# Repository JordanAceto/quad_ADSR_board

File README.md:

# Quad digital ADSR module

# *** Work in progress ***

## ADSRs are generated by an STM32 microcontroller and controlled by four encoders. A seven-segment display shows the most recently modified parameter.

One ADSR at a time is set as the "active" ADSR, which will be controlled by the encoders.

To select an ADSR as "active", the encoder push-button above a given ADSR is pressed.

The four-digit seven-segment display shows the parameter of the encoder that was most recently turned. For instance, if you just turned the decay time to 500 milliseconds, the display will show `0.500`. If you then adjust the sustain level to 68%, the display will now show `  68`. Time based parameters are shown in units of seconds, and sustain parameters are shown as 0% to 100%.

Additionally, the ADSRs can all be forced to lock to a "master" ADSR, so that that their attack, decay, sustain, and release parameters are all set the same. The four ADSRs can still be triggered independently in this mode, which makes this useful for polyphonic patches. This saves you from manually setting identical paramters four times. Lock-to-master mode is selected by performing a long push-switch press of the encoder above the desired ADSR. For instance, to force all the ADSRs to lock to the ADSR 3 settings, depress and hold the sustain encoder push-button for a few seconds. To leave lock-to-master mode, do a short click of any of the encoder push-buttons to select a new active ADSR.

A bank of four bi-color LEDs shows the active ADSR, and whether it is in independent, or lock-to-master mode.

# First rev build evaluation:
- Most of the systems work.
- __Done__ (but there is an I2C bug lurking, see the issues)~~The EEPROM has not been physically installed and EEPROM code has not been written yet.~~
- __DONE__ ~~In the code, when switching from lock-to-master mode back to independent mode: the ADSRs should go back to the settings they held before entering lock-to-master mode. Write a function called `release_ADSRs_from_master_mode` or something that accomplishes this, and call that function when leaving lock-to-master mode~~.
- __Done__ ~~The encoders should be no-detent types. I used encoders with detents and I don't like it.~~
- I tried and failed to setup encoder trigger filtering, please investigate using the timer register filters when the timers are in encoder mode. I'd like to be able to apply filtering to the encoders. They work fine and don't misfire now, but it would be nice to easily tailor how "fast" they update by addign in some filtering.
- __This really isn't that bad__ ~~The heights of the panel mount components is an issue: the 3.5mm jacks are taller than the encoders and the seven-segment display. I got everything to work by lifting the encoders and 7-seg up off the pcb before soldering, but this is lame. I think the solution is split the pcb into a main pcb and a jack pcb, and connect the two pcbs with wires. Another solution could be to create a "lifter" pcb that acts as a spacer between the main pcb and the encoders/7-seg, but this seems kind of yucky too. Think about this for a while before doing a new pcb rev.~~
- I'm having issues with getting the PLL to work for arbitrary frequencies: with some settings of M, N, and P the output frequency is not as expected. Please investigate this and figure out what I'm doing wrong.
- I used two MCP4822 DACs, but I probably could have used the 2 internal DAC channels for 2 of the ADSRs and only installed one MCP4822. Investigate if using the internal DAC for 2 channels creates any pinout conflicts, or any other kind of conflicts, for the next board revision, to try and save a DAC.
- The ADSR outputs are low: I want 10v peak ADSRs and I calculated the opamp gain resistors assuming the DACs output 3.3v peaks, but they don't. Please recalculate the gain resistors for the actual MCP4822 output with a gain of 1x. Take into account the internal DACs if you apply the suggestion above.
- __DONE__ (enabled FPU and changed signals to floats) ~~Many parts of the codebase could be optimized and improved. In particular, the ADSR code does some costly 64-bit divisions in a couple of spots. See if you can't improve this. View the `main.list` output file occasionally~~.
- __DONE__ (works ok but be on the lookout) ~~Compiler optimization is turned off right now. Turn this up to `-Os` or `-O2` and make sure that nothing breaks. There might be some volatile issues, or necessary code that gets optimized away, be careful and thorough!~~
- Otherwise the project is in pretty good shape! The prototype I built could definitely go in a rack and work with other modules.

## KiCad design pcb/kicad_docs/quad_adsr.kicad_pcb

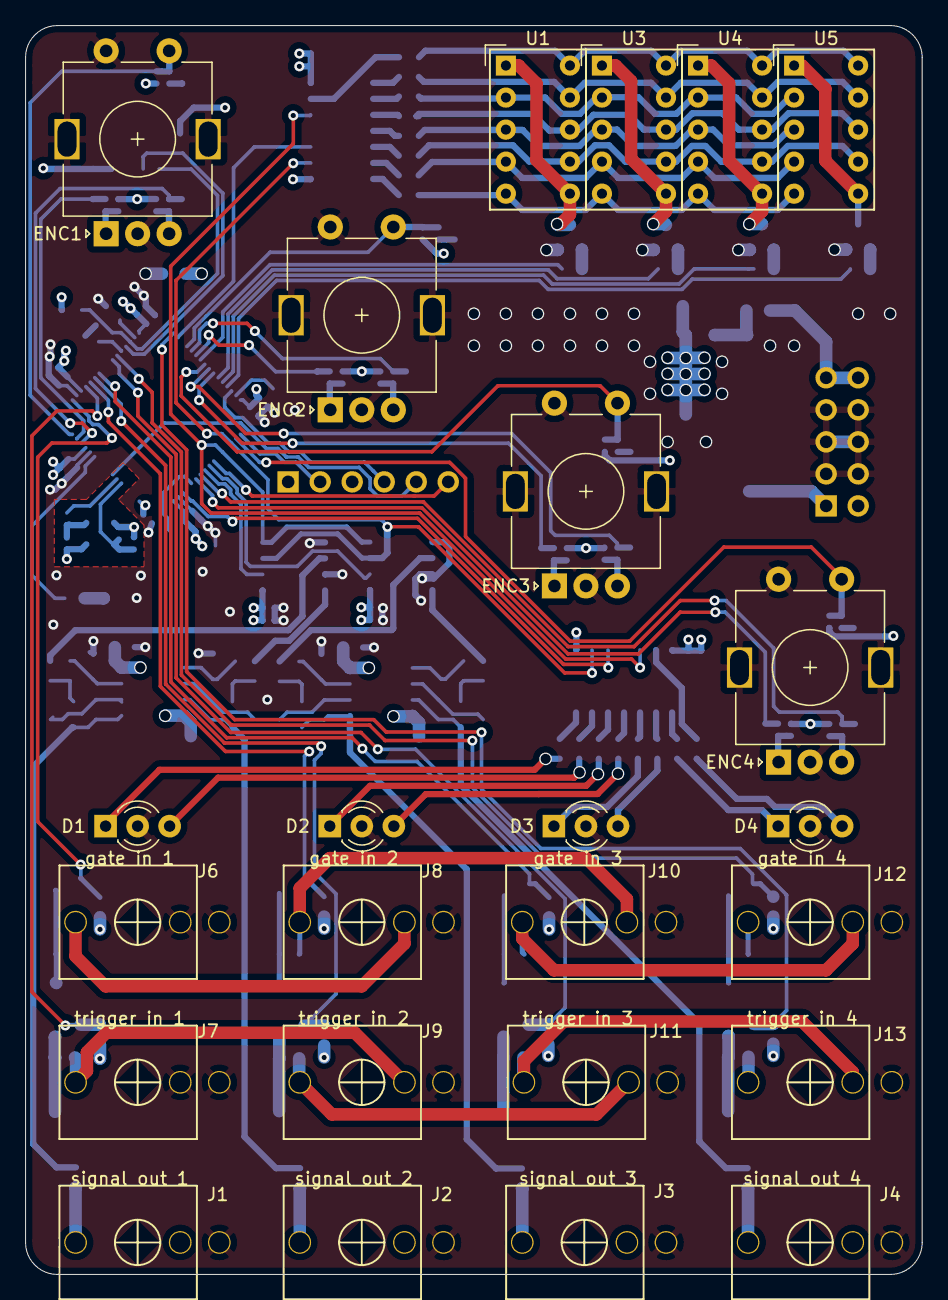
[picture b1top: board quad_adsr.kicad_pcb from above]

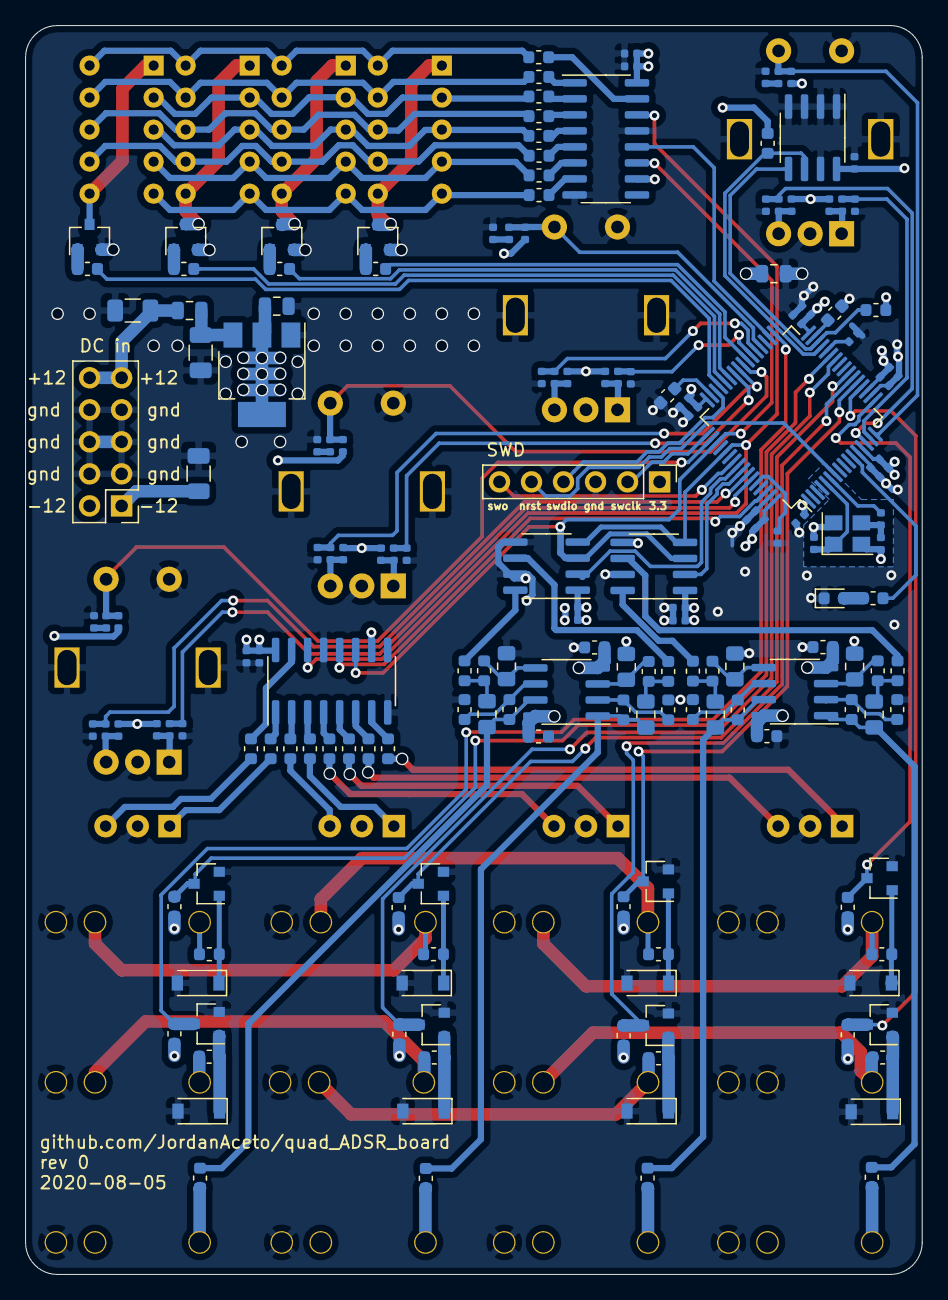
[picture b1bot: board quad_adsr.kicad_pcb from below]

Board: 4 copper layers, 71.1 x 99.1 mm, 197 parts (173 on the bottom side), 142 nets.

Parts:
C1, C2, C4, C5, C7, C8, C10, C11: 10nF; C_0402_1005Metric
C3, C6, C9, C12, C16, C17, C18, C19, C20, C21, C22, C23, C24, C25, C26, C27, C28, C29, C30, C31, C32, C49, C50, C53: 100nF; C_0402_1005Metric
C13, C51, C52: 10uF; C_1206_3216Metric
C14, C15: 10uF; C_0805_2012Metric
C33, C34, C35, C36: 100nF; C_0603_1608Metric
C37, C38, C39, C40, C41, C42, C43, C44: 2n2; C_0805_2012Metric_Pad1.15x1.40mm_HandSolder
C45, C46: 2.2uF; C_0603_1608Metric
C47, C48: 12pF; C_0402_1005Metric
D1, D2, D3, D4: LED_Dual_ACA; LED_D3.0mm-3
D5: LED; LED_0603_1608Metric
D6, D7, D8, D9, D10, D11, D12, D13: 1N4148W; D_SOD-123
ENC1, ENC2, ENC3, ENC4: Rotary_Encoder_Switch; RotaryEncoder_Alps_EC11E-Switch_Vertical_H20mm
FB1: Ferrite_Bead_Small; L_0805_2012Metric
HSE1: 16MHz; Crystal_SMD_3225-4Pin_3.2x2.5mm
J1, J2, J3, J4: PJ301M-12
J5: power_in; PinHeader_2x05_P2.54mm_Vertical
J6: gate_1_i n; PJ301M-12
J7: trigger_1_in; PJ301M-12
J8: gate_2_in; PJ301M-12
J9: trigger_2_in; PJ301M-12
J10: gate_3_in; PJ301M-12
J11: trigger_3_in; PJ301M-12
J12: gate_4_in; PJ301M-12
J13: trigger_4_in; PJ301M-12
J14: SWD_header; PinHeader_1x06_P2.54mm_Vertical
Q1, Q2, Q3, Q4, Q5, Q6, Q7, Q8, Q9, Q10, Q11, Q12: MMBT3904; SOT-23
R1, R2, R3, R4, R7, R8, R9, R10, R13, R14, R15, R16, R19, R20, R21, R22, R82, R83: 10k; R_0402_1005Metric
R5, R11, R17, R23: 4k7; R_0402_1005Metric
R6, R12, R18, R24, R84: 100; R_0402_1005Metric
R25, R34, R35, R36, R50, R52, R54, R56, R58, R60, R62, R64: 10k; R_0603_1608Metric
R26, R27, R28, R29, R30, R31, R32, R33, R37, R38, R39, R40, R41, R42, R43, R44: 390; R_0603_1608Metric
R45, R46, R47, R48: 1k; R_0603_1608Metric
R49, R51, R53, R55, R57, R59, R61, R63: 100k; R_0603_1608Metric
R65, R66, R73, R74: 50k; R_0603_1608Metric
R67, R68, R75, R76: 200k; R_0603_1608Metric
R69, R70, R77, R78: 33k; R_0603_1608Metric
R71, R72, R79, R80: 68k; R_0603_1608Metric
R81: 2k2; R_0603_1608Metric
R85, R86: 4k7; R_0603_1608Metric
U1, U3, U4, U5: HDSP-7503; HDSP-A151
U2, U6: 74HC595; SOIC-16_3.9x9.9mm_P1.27mm
U7: AMS1117-3.3; SOT-223-3_TabPin2
U8, U11: TL072; SOIC-8_3.9x4.9mm_P1.27mm
U9, U10: MCP4822; SOIC-8_3.9x4.9mm_P1.27mm
U12: STM32F405RGTx; LQFP-64_10x10mm_P0.5mm
U13: 24LC32; SOIC-8_3.9x4.9mm_P1.27mm

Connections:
+3V3: C14.1, C15.1, C16.1, C17.1, C18.1, C19.1, C20.1, C21.1, C22.1, C23.1, C24.1, C25.1, C26.1, C27.1, C28.1, C29.1, C30.1, C31.1, C32.1, C49.1, C50.1, C53.1, J14.1, R2.1, R3.1, R5.2, R8.1, R9.1, R11.1, R14.1, R15.1, R17.2, R20.1, R21.1, R23.1, R50.1, R52.1, R54.1, R56.1, R58.1, R60.1, R62.1, R64.1, R85.1, R86.1, U2.10, U2.16, U6.10, U6.16, U7.2, U9.1, U10.1, U12.1, U12.13, U12.19, U12.32, U12.48, U12.64, U13.8
+12V: C33.1, C35.1, C51.1, FB1.2, J5.9, J5.10, U8.8, U11.8
-12V: C34.2, C36.2, C52.2, J5.1, J5.2, U8.4, U11.4
/EEPROM/I2C2_SCL: R86.2, U12.29, U13.6
/EEPROM/I2C2_SDA: R85.2, U12.30, U13.5
/encoders/enc_1_a_out: C1.1, R1.2, U12.14
/encoders/enc_1_b_out: C2.1, R4.2, U12.15
/encoders/enc_1_sw_out: ENC1.S1, R5.1, R6.1, U12.16
/encoders/enc_2_a_out: C4.1, R7.2, U12.37
/encoders/enc_2_b_out: C5.1, R10.2, U12.38
/encoders/enc_2_sw_out: ENC2.S1, R11.2, R12.1, U12.36
/encoders/enc_3_a_out: C7.1, R13.2, U12.41
/encoders/enc_3_b_out: C8.1, R16.2, U12.42
/encoders/enc_3_sw_out: ENC3.S1, R17.1, R18.1, U12.40
/encoders/enc_4_a_out: C10.1, R19.2, U12.58
/encoders/enc_4_b_out: C11.1, R22.2, U12.59
/encoders/enc_4_sw_out: ENC4.S1, R23.2, R24.1, U12.50
/input_jacks/g_2_normalization: J8.3, J10.2, R53.2
/input_jacks/t_2_normalization: J9.3, J11.2, R55.2
/leds/QA: R37.2, U6.15
/leds/QB: R38.2, U6.1
/leds/QC: R39.2, U6.2
/leds/QD: R40.2, U6.3
/leds/QE: R41.2, U6.4
/leds/QF: R42.2, U6.5
/leds/QG: R43.2, U6.6
/leds/QH: R44.2, U6.7
/leds/spi_clk_in: U2.11, U6.11, U9.3, U10.3, U12.51
/leds/spi_data_in: U2.14, U6.14, U9.4, U10.4, U12.53
/leds/spi_rg_leds_cs: U6.12, U12.62
/seven_segment_display/digit_1_in: R25.2, U12.39
/seven_segment_display/digit_2_in: R34.2, U12.43
/seven_segment_display/digit_3_in: R35.2, U12.44
/seven_segment_display/digit_4_in: R36.2, U12.45
/seven_segment_display/segment_A: R26.1, U1.10, U3.10, U4.10, U5.10
/seven_segment_display/segment_B: R27.1, U1.9, U3.9, U4.9, U5.9
/seven_segment_display/segment_C: R29.1, U1.8, U3.8, U4.8, U5.8
/seven_segment_display/segment_D: R33.1, U1.5, U3.5, U4.5, U5.5
/seven_segment_display/segment_DP: R31.1, U1.7, U3.7, U4.7, U5.7
/seven_segment_display/segment_E: R32.1, U1.4, U3.4, U4.4, U5.4
/seven_segment_display/segment_F: R28.1, U1.2, U3.2, U4.2, U5.2
/seven_segment_display/segment_G: R30.1, U1.3, U3.3, U4.3, U5.3
/seven_segment_display/spi_seven_segment_cs: U2.12, U12.34
/spi_dacs_and_level_shifters/10vp_adsr_1_out: C39.1, R45.2, R71.1, U8.1
/spi_dacs_and_level_shifters/10vp_adsr_2_out: C43.1, R46.2, R79.1, U8.7
/spi_dacs_and_level_shifters/10vp_adsr_3_out: C40.1, R47.2, R72.1, U11.1
/spi_dacs_and_level_shifters/10vp_adsr_4_out: C44.1, R48.2, R80.1, U11.7
/spi_dacs_and_level_shifters/adsr_1_3.3v: R66.2, U9.6
/spi_dacs_and_level_shifters/adsr_2_3.3v: R74.2, U9.8
/spi_dacs_and_level_shifters/adsr_3_3.3v: R65.2, U10.6
/spi_dacs_and_level_shifters/adsr_4_3.3v: R73.2, U10.8
/spi_dacs_and_level_shifters/spi_dac1_cs: U9.2, U12.57
/spi_dacs_and_level_shifters/spi_dac2_cs: U10.2, U12.56
/stmf32/NRST: J14.5, U12.7
/stmf32/PH1: R84.1, U12.6
/stmf32/PHO: C47.1, HSE1.1, U12.5
/stmf32/SWCLK: J14.2, U12.49
/stmf32/SWDIO: J14.4, U12.46
/stmf32/SWO: J14.6, U12.55
/stmf32/gate_1_in: Q5.3, R50.2, U12.17
/stmf32/gate_2_in: Q7.3, R54.2, U12.21
/stmf32/gate_3_in: Q9.3, R58.2, U12.23
/stmf32/gate_4_in: Q11.3, R62.2, U12.27
/stmf32/status_led: R81.1, U12.11
/stmf32/trigger_1_in: Q6.3, R52.2, U12.20
/stmf32/trigger_2_in: Q8.3, R56.2, U12.22
/stmf32/trigger_3_in: Q10.3, R60.2, U12.26
/stmf32/trigger_4_in: Q12.3, R64.2, U12.33
GND: C1.2, C2.2, C3.2, C4.2, C5.2, C6.2, C7.2, C8.2, C9.2, C10.2, C11.2, C12.2, C13.2, C14.2, C15.2, C16.2, C17.2, C18.2, C19.2, C20.2, C21.2, C22.2, C23.2, C24.2, C25.2, C26.2, C27.2, C28.2, C29.2, C30.2, C31.2, C32.2, C33.2, C34.1, C35.2, C36.1, C37.2, C38.2, C41.2, C42.2, C45.2, C46.2, C47.2, C48.2, C49.2, C50.2, C51.2, C52.1, C53.2, D1.2, D2.2, D3.2, D4.2, D5.1, D6.2, D7.2, D8.2, D9.2, D10.2, D11.2, D12.2, D13.2, ENC1.C, ENC1.MP, ENC1.S2, ENC2.C, ENC2.MP, ENC2.S2, ENC3.C, ENC3.MP, ENC3.S2, ENC4.C, ENC4.MP, ENC4.S2, HSE1.2, HSE1.4, J1.1, J2.1, J3.1, J4.1, J5.3, J5.4, J5.5, J5.6, J5.7, J5.8, J6.1, J6.2, J7.1, J7.2, J8.1, J9.1, J10.1, J11.1, J12.1, J13.1, J14.3, Q1.2, Q2.2, Q3.2, Q4.2, Q5.2, Q6.2, Q7.2, Q8.2, Q9.2, Q10.2, Q11.2, Q12.2, R69.1, R70.1, R77.1, R78.1, R82.2, R83.2, U2.8, U2.13, U6.8, U6.13, U7.1, U9.5, U9.7, U10.5, U10.7, U12.12, U12.18, U12.63, U13.1, U13.2, U13.3, U13.4, U13.7
unnamed: C3.1, R6.2
unnamed: C6.1, R12.2
unnamed: C9.1, R18.2
unnamed: C12.1, R24.2
unnamed: C13.1, FB1.1, U7.3
unnamed: C37.1, R67.1, U11.3
unnamed: C38.1, R68.1, U8.3
unnamed: C39.2, R66.1, R68.2
unnamed: C40.2, R65.1, R67.2
unnamed: C41.1, R75.1, U11.5
unnamed: C42.1, R76.1, U8.5
unnamed: C43.2, R74.1, R76.2
unnamed: C44.2, R73.1, R75.2
unnamed: C45.1, U12.31
unnamed: C46.1, U12.47
unnamed: C48.1, HSE1.3, R84.2
unnamed: D1.1, R44.1
unnamed: D1.3, R43.1
unnamed: D2.1, R42.1
unnamed: D2.3, R41.1
unnamed: D3.1, R40.1
unnamed: D3.3, R39.1
unnamed: D4.1, R38.1
unnamed: D4.3, R37.1
unnamed: D5.2, R81.2
unnamed: D6.1, Q5.1, R49.1
unnamed: D7.1, Q6.1, R51.1
unnamed: D8.1, Q7.1, R53.1
unnamed: D9.1, Q8.1, R55.1
unnamed: D10.1, Q9.1, R57.1
unnamed: D11.1, Q10.1, R59.1
unnamed: D12.1, Q11.1, R61.1
unnamed: D13.1, Q12.1, R63.1
unnamed: ENC1.A, R3.2, R4.1
unnamed: ENC1.B, R1.1, R2.2
unnamed: ENC2.A, R9.2, R10.1
unnamed: ENC2.B, R7.1, R8.2
unnamed: ENC3.A, R15.2, R16.1
unnamed: ENC3.B, R13.1, R14.2
unnamed: ENC4.A, R21.2, R22.1
unnamed: ENC4.B, R19.1, R20.2
unnamed: J1.3, R45.1
unnamed: J2.3, R46.1
unnamed: J3.3, R47.1
unnamed: J4.3, R48.1
unnamed: J6.3, J8.2, R49.2
unnamed: J7.3, J9.2, R51.2
unnamed: J10.3, J12.2, R57.2
unnamed: J11.3, J13.2, R59.2
unnamed: J12.3, R61.2
unnamed: J13.3, R63.2
unnamed: Q1.1, R25.1
unnamed: Q1.3, U1.1, U1.6
unnamed: Q2.1, R34.1
unnamed: Q2.3, U3.1, U3.6
unnamed: Q3.1, R35.1
unnamed: Q3.3, U4.1, U4.6
unnamed: Q4.1, R36.1
unnamed: Q4.3, U5.1, U5.6
unnamed: R26.2, U2.15
unnamed: R27.2, U2.1
unnamed: R28.2, U2.2
unnamed: R29.2, U2.3
unnamed: R30.2, U2.4
unnamed: R31.2, U2.5
unnamed: R32.2, U2.6
unnamed: R33.2, U2.7
unnamed: R69.2, R71.2, U8.2
unnamed: R70.2, R72.2, U11.2
unnamed: R77.2, R79.2, U8.6
unnamed: R78.2, R80.2, U11.6
unnamed: R82.1, U12.60
unnamed: R83.1, U12.28

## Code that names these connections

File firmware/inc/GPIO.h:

/*
--|----------------------------------------------------------------------------|
--| FILE DESCRIPTION:
--|   GPIO.h provides the interface for initializing the GPIO pins.
--|   
--| 
--|----------------------------------------------------------------------------|
--| REFERENCES:
--|
--|----------------------------------------------------------------------------|
*/

#ifndef GPIO_H_INCLUDED
#define GPIO_H_INCLUDED

/*
--|----------------------------------------------------------------------------|
--| INCLUDE FILES
--|----------------------------------------------------------------------------|
*/

#include "stm32f4xx.h"

/*
--|----------------------------------------------------------------------------|
--| PUBLIC DEFINES
--|----------------------------------------------------------------------------|
*/

// defines for GPIO pins used by the system follow the pattern below:

/*
--| NAME: xxx_Port
--| DESCRIPTION: the GPIO port for a given GPIO pin
--| TYPE: GPIO_TypeDef *
*/

/*
--| NAME: xxx_Pin
--| DESCRIPTION: the pin number for a given GPIO pin
--| TYPE: uint
*/

/*
--|------------------------------------------|
--| ENCODER PINS
--|------------------------------------------|
*/

/*
--| Encoder 1
*/
#define ENCODER_1_A_GPIO_Port (GPIOA)
#define ENCODER_1_A_Pin (0u)

#define ENCODER_1_B_GPIO_Port (GPIOA)
#define ENCODER_1_B_Pin (1u)

#define ENCODER_1_SWITCH_GPIO_Port (GPIOA)
#define ENCODER_1_SWITCH_Pin (2u)

/*
--| Encoder 2
*/
#define ENCODER_2_A_GPIO_Port (GPIOC)
#define ENCODER_2_A_Pin (6u)

#define ENCODER_2_B_GPIO_Port (GPIOC)
#define ENCODER_2_B_Pin (7u)

#define ENCODER_2_SWITCH_GPIO_Port (GPIOB)
#define ENCODER_2_SWITCH_Pin (15u)

/*
--| Encoder 3
*/
#define ENCODER_3_A_GPIO_Port (GPIOA)
#define ENCODER_3_A_Pin (8u)

#define ENCODER_3_B_GPIO_Port (GPIOA)
#define ENCODER_3_B_Pin (9u)

#define ENCODER_3_SWITCH_GPIO_Port (GPIOC)
#define ENCODER_3_SWITCH_Pin (9u)

/*
--| Encoder 4
*/
#define ENCODER_4_A_GPIO_Port (GPIOB)
#define ENCODER_4_A_Pin (6u)

#define ENCODER_4_B_GPIO_Port (GPIOB)
#define ENCODER_4_B_Pin (7u)

#define ENCODER_4_SWITCH_GPIO_Port (GPIOA)
#define ENCODER_4_SWITCH_Pin (15u)

/*
--|------------------------------------------|
--| GATE PINS
--|------------------------------------------|
*/

/*
--| Gate 1
*/
#define GATE_1_GPIO_Port (GPIOA)
#define GATE_1_Pin (3u)

/*
--| Gate 2
*/
#define GATE_2_GPIO_Port (GPIOA)
#define GATE_2_Pin (5u)

/*
--| Gate 3
*/
#define GATE_3_GPIO_Port (GPIOA)
#define GATE_3_Pin (7u)

/*
--| Gate 4
*/
#define GATE_4_GPIO_Port (GPIOB)
#define GATE_4_Pin (1u)

/*
--|------------------------------------------|
--| TRIGGER PINS
--|------------------------------------------|
*/

/*
--| Trigger 1
*/
#define TRIG_1_GPIO_Port (GPIOA)
#define TRIG_1_Pin (4u)

/*
--| Trigger 2
*/
#define TRIG_2_GPIO_Port (GPIOA)
#define TRIG_2_Pin (6u)

/*
--| Trigger 3
*/
#define TRIG_3_GPIO_Port (GPIOB)
#define TRIG_3_Pin (0u)

/*
--| Trigger 4
*/
#define TRIG_4_GPIO_Port (GPIOB)
#define TRIG_4_Pin (12u)

/*
--|------------------------------------------|
--| SPI3 PINS
--|------------------------------------------|
*/

/*
--| SPI3 SCK
*/
#define SPI3_SCK_GPIO_Port (GPIOC)
#define SPI3_SCK_Pin (10u)

/*
--| SPI3 MISO
*/
#define SPI3_MISO_GPIO_Port (GPIOC)
#define SPI3_MISO_Pin (11u)

/*
--| SPI3 MOSI
*/
#define SPI3_MOSI_GPIO_Port (GPIOC)
#define SPI3_MOSI_Pin (12u)

/*
--| SPI3 DAC 1 CS
*/
#define SPI3_DAC1_CS_GPIO_Port (GPIOB)
#define SPI3_DAC1_CS_Pin (5u)

/*
--| SPI3 DAC 2 CS
*/
#define SPI3_DAC2_CS_GPIO_Port (GPIOB)
#define SPI3_DAC2_CS_Pin (4u)

/*
--| SPI3 SEVEN SEGMENT DISPLAY CS
*/
#define SPI3_SEVEN_SEG_CS_GPIO_Port (GPIOB)
#define SPI3_SEVEN_SEG_CS_Pin (13u)

/*
--| SPI3 RED/GREEN LEDS CS
*/
#define SPI3_RG_LEDS_CS_GPIO_Port (GPIOB)
#define SPI3_RG_LEDS_CS_Pin (9u)

/*
--|------------------------------------------|
--| SEVEN SEGMENT DIGIT SELECT PINS
--|------------------------------------------|
*/

/*
--| SEVEN SEGMENT DIGIT 1 SELECT
*/
#define SEVEN_SEG_DIGIT_1_GPIO_Port (GPIOC)
#define SEVEN_SEG_DIGIT_1_Pin (8u)

/*
--| SEVEN SEGMENT DIGIT 2 SELECT
*/
#define SEVEN_SEG_DIGIT_2_GPIO_Port (GPIOA)
#define SEVEN_SEG_DIGIT_2_Pin (10u)

/*
--| SEVEN SEGMENT DIGIT 3 SELECT
*/
#define SEVEN_SEG_DIGIT_3_GPIO_Port (GPIOA)
#define SEVEN_SEG_DIGIT_3_Pin (11u)

/*
--| SEVEN SEGMENT DIGIT 4 SELECT
*/
#define SEVEN_SEG_DIGIT_4_GPIO_Port (GPIOA)
#define SEVEN_SEG_DIGIT_4_Pin (12u)

/*
--|------------------------------------------|
--| I2C2 PINS
--|------------------------------------------|
*/

/*
--| I2C2 SCL
*/
#define I2C2_SCL_GPIO_Port (GPIOB)
#define I2C2_SCL_Pin (10u)

/*
--| I2C2 SDA
*/
#define I2C2_SDA_GPIO_Port (GPIOB)
#define I2C2_SDA_Pin (11u)

/*
--|------------------------------------------|
--| MISC/DEBUG PINS
--|------------------------------------------|
*/

/*
--| Status LED
*/
#define STATUS_LED_GPIO_Port (GPIOC)
#define STATUS_LED_Pin (3u)

/*
--|----------------------------------------------------------------------------|
--| PUBLIC FUNCTION PROTOTYPES
--|----------------------------------------------------------------------------|
*/

/*------------------------------------------------------------------------------
Function Name:
    GPIO_Init

Function Description:
    Perform initialization of the GPIO pins used by the system.

Parameters:
    None

Returns:
    None

Assumptions/Limitations:
    Assumed that this will be called before using any of the GPIO pins.
------------------------------------------------------------------------------*/
void GPIO_Init(void);

#endif

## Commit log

2020-03-02 add pdf of cortex m3 ref manual
2020-05-29 move stm32 docs into their own directory
2020-05-29 add misc datasheets
2020-05-29 remove redundant stm32 docs
2020-05-29 change encoder push-button switch passives
2020-06-25 add EEPROM, big pcb re-design
2020-06-29 spread out 1/8" jacks
2020-06-29 add gitignore, remove unnecesary kicad files
2020-06-29 remove more redundant kicad files
2020-06-29 replace accidentally deleted kicad file
2020-07-14 add front panel, rearrange directories
2020-07-31 add title blocks, fix some erc violations
2020-07-31 generate schemtic pdf
2020-07-31 add rendered pcb pics
2020-07-31 add readme
2020-08-05 increase font size
2020-08-05 add github url and rev info to silk
2020-08-05 change LED current limiting resistors
2020-08-05 small pcb treaks
2020-08-18 add title block to front panel
2020-08-18 reorganize directory structure, add some pics
2020-08-19 add pin 1 locations to silk
2020-08-19 regenerate schematic with new LED resistors
2020-08-19 generate interactive BOM
2020-08-19 generate jlcpcb assembly docs
2020-08-19 generate gerbers
2020-08-26 add front panel gerbers
2020-08-26 start on firmware
2020-08-26 update gitignore to ignore compiled objects
2020-08-27 add GPIO pin defines, move SPI pin init code to GPIO.c
2020-08-27 update SPI chip select init
2020-08-27 add I2C GPIO pin init code, parenthesize for consistency
2020-08-27 clean up formatting
2020-08-27 add seven segment software module
2020-08-27 add comment about 7-segment datasheet
2020-08-27 fix comment ommision
2020-08-27 add bi-color LED software module
2020-08-27 add ADSR software module
2020-08-27 remove c++ stuff from makefile, change optimization to -Os
2020-08-27 change optimazation back to -O0, -Os broke SPI, pls investigate
2020-08-27 clarify comments
2020-08-28 add readme to reference_docs
2020-08-28 add readme for hardware dir
2020-08-28 flesh out main_pcb readme
2020-08-28 add beginnings of firmware readme
2020-08-28 update main to demo basic features
2020-08-28 add RCC init code
2020-08-28 fix bug caused by DAC2 CS pin sharing NJTRST line
2020-08-28 fix SPI bug where CS went high too soon
2020-08-28 typo
2020-08-28 add TIM7 module
2020-08-28 add interrupts module
2020-08-28 initialize TIM7 and interrupts
2020-08-28 add TI6 module
2020-08-28 add TIm6 interrupts
2020-08-28 initialize TI6
2020-08-29 add sysTick software module
2020-08-29 add SysTick src
2020-08-29 use SysTick for demo
2020-08-29 shuffle RCC code around, something is wrong with the clock freq
2020-08-29 work on bug where pll frequency is wrong
2020-08-29 add global dta
2020-08-29 add global_data.c file
2020-08-29 add input processing software module
2020-08-29 add output processing software module
2020-08-29 make provate fcns static, make input update fcn public
2020-08-29 add encoder software module
2020-08-29 move encoder scaling out of input_processing
2020-08-29 initialize encoders
2020-08-29 initialize encoder pins
2020-08-29 remove unneded syscalls module
2020-08-30 get the basics of the application working
2020-08-30 move fcn call abover where it is needed
2020-08-30 make encoders count the correct direction
2020-08-30 fix bicolor LED bug
2020-08-30 fix bugs in seven-segment-display
2020-08-31 add first rev build notes to README
2021-06-01 tidy up update_ADSR_inputs fcn
2021-06-01 rename and tidy up set-encoders fcn
2021-06-02 restore setting when leaving lock-to-master mode
2021-06-02 make set-encoders-to-active-adsr fcn private
2021-06-02 update readme after improving lock-to-master return
2021-06-02 disable interrupts during SPI transmit
2021-06-02 fix bug with lock-to-master transition
2021-06-03 remove unused fcns
2021-06-03 make fcn public again to fix startup bug
2021-06-03 add firmware size script
2021-06-03 add lookup table generator script
2021-06-03 use python generated lookup tables
2021-06-03 increase LUT length
2021-06-03 remove misleading state machine cases
2021-06-03 use interrupt flags, extract code from ISRs into main
2021-06-03 change opt to -0s
2021-06-04 clean up tuning word calculation
2021-06-04 enable FPU
2021-06-04 add MCP4822 full scale definition
2021-06-04 LUTs now range [0.0, 1.0]
2021-06-04 convert ADSR output to float in range [0.0, 1.0]
2021-06-04 scale DACs for float inputs
2021-06-04 update readme after change to floats
2021-06-04 tidy up includes
2021-06-04 include tidy up
2021-06-04 move CMSIS to 3rd party dir, add make commands
2021-06-05 fix outdated comment
2021-06-05 move startup asm file to third-party
2021-06-08 refine python LUT generator
2021-06-10 add clock speed definitions
2021-06-10 add I2C2 module
2021-06-10 initialize I2C2
2021-06-10 add 24LC32 EEPROM module
2021-06-17 attempt to fix I2C2 bug, not successful
2021-06-17 add EEPROM timer object
2021-06-17 make interrupt flag setters private
2021-06-17 add self test function to EEPROM
2021-06-17 add EEPROM functions
2021-06-17 add EEPROM init, move irq enable
2021-06-17 add EEPROM test and writes to main
2021-06-17 fix docstring mistake
2021-06-17 remove unused import
2021-06-17 uodate firmware readme
2021-06-17 reorder pdf schematic pages
2021-06-17 remove test code
2021-06-20 add photos
2021-06-20 add pics to readme
2021-07-03 big code reorganization
2021-07-03 add scope shot
2021-12-20 tidy up ADSR.h comments, remove unused func sig
